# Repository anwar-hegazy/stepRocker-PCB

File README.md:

# stepRocker-PCB
Eagle Design Files for the stepRocker Stepper Driver Board

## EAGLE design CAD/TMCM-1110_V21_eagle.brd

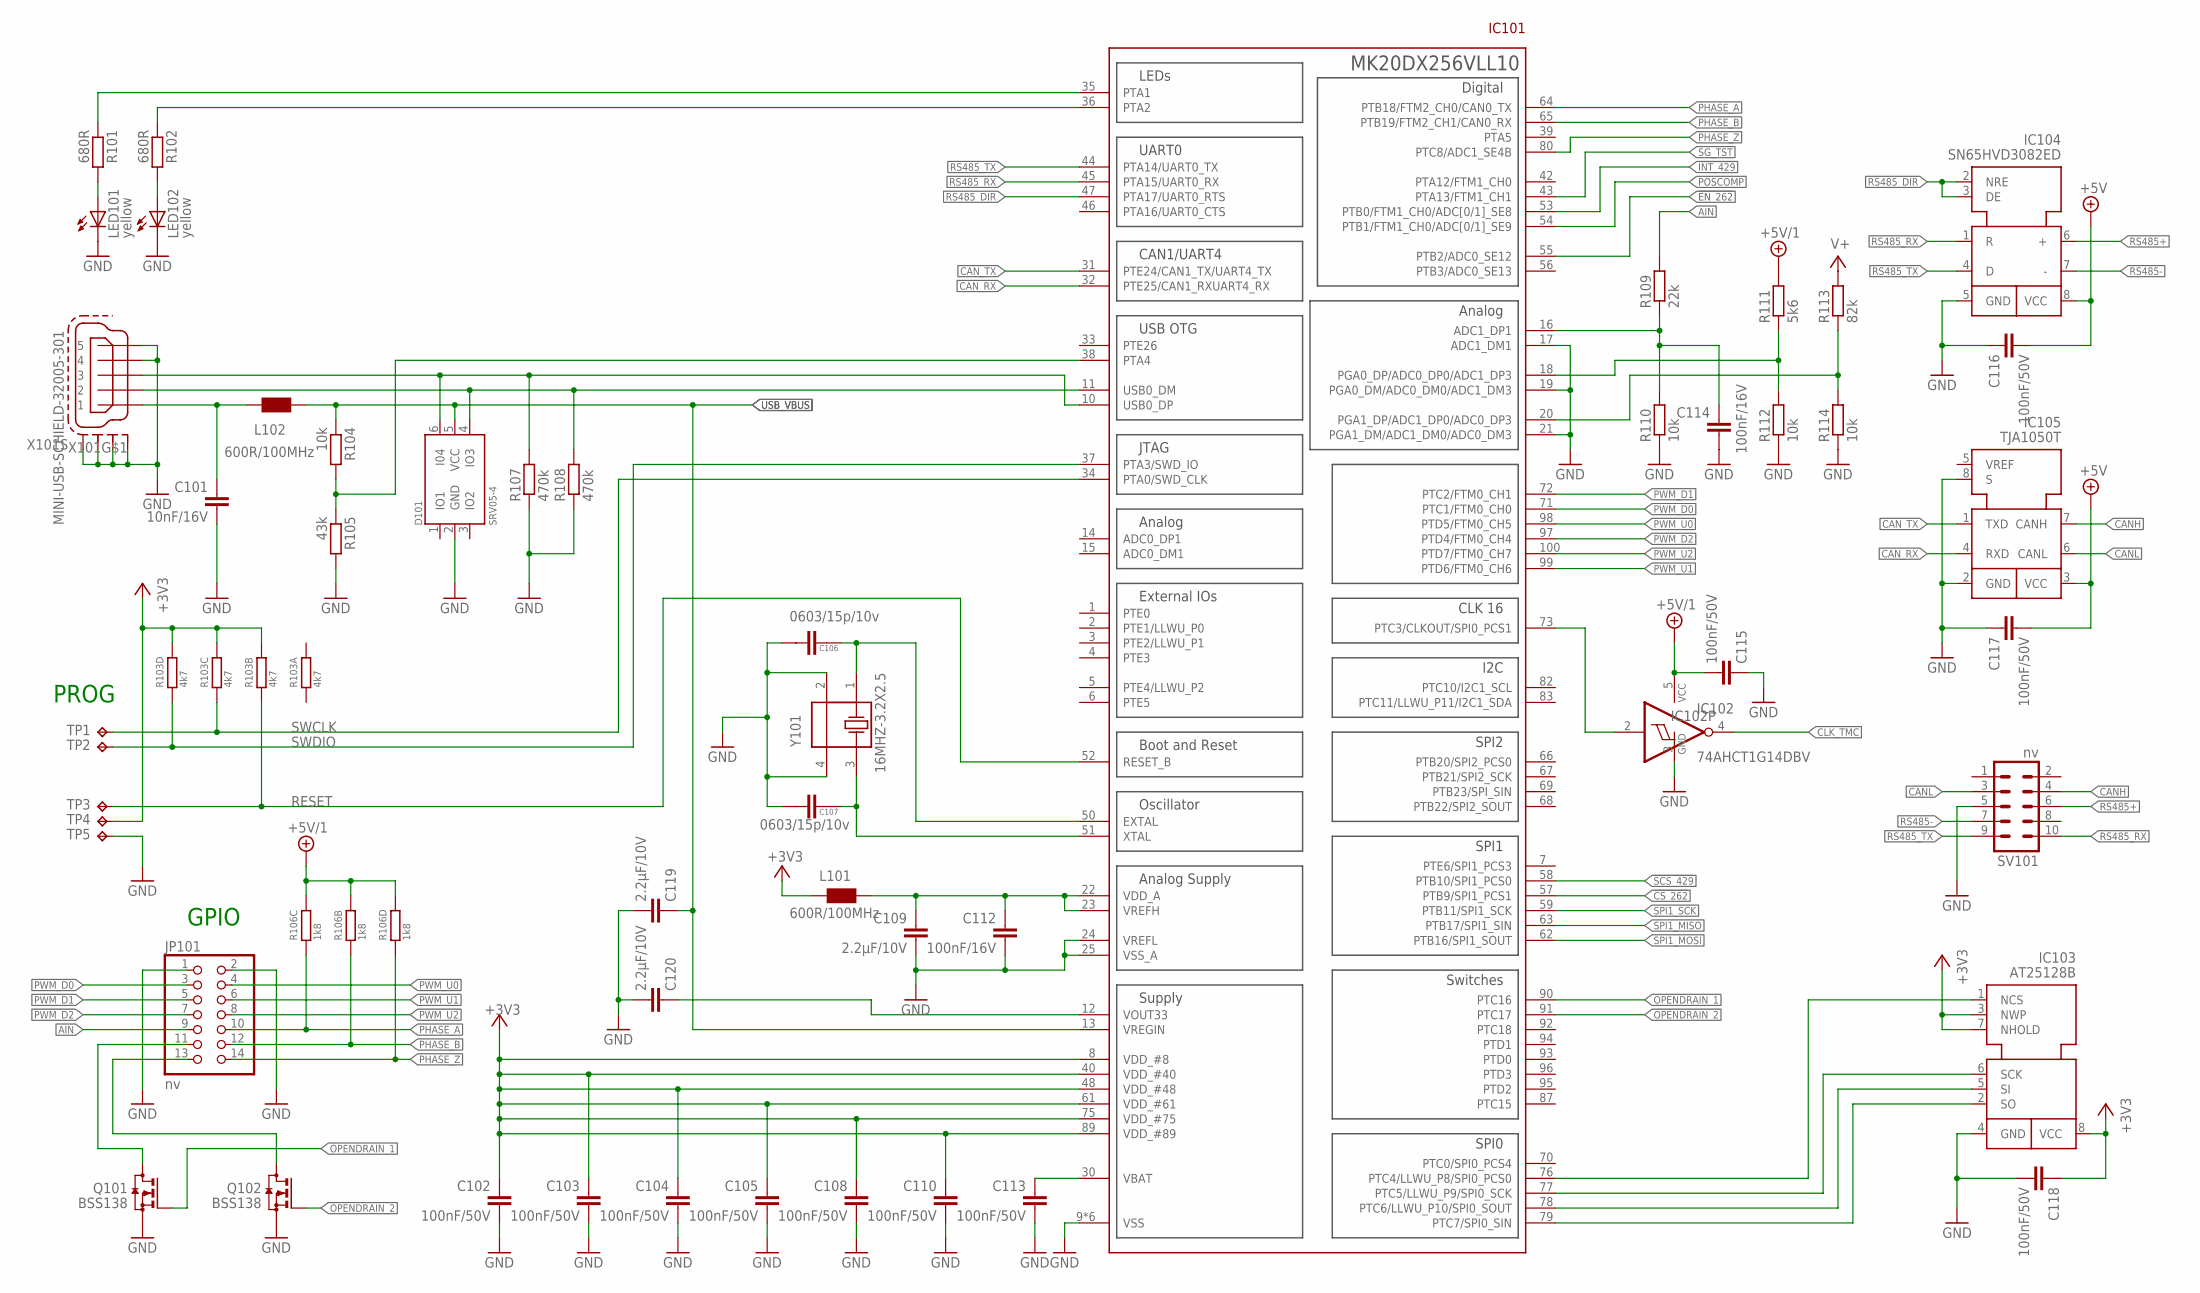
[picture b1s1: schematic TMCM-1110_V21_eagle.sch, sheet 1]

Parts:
C101: 10nF/16V; C0603
C102, C103, C104, C105, C108, C110, C113, C115, C116, C117, C118: 100nF/50V; C0603
C106, C107: 0603/15p/10v; 0603
C109, C119, C120: 2.2µF/10V; C0603
C112, C114: 100nF/16V; C0603
D101: SRV05-4; TMC_SOT23-6
IC101: MK20DX256VLL10; TMC_LQFP100
IC102: 74AHCT1G14DBV; SOT23-5
IC103: AT25128B; SO8
IC104: SN65HVD3082ED; SO8
IC105: TJA1050T; SO8
JP101: nv; 2X07
L101, L102: 600R/100MHz; 0603
LED101, LED102: yellow; CHIP-LED0603
Q101, Q102: BSS138; SOT23
R101, R102: 680R; R0603
R103: 4k7; R_4X_1206
R104, R110, R112, R114: 10k; R0603
R105: 43k; R0603
R106: 1k8; R_4X_1206
R107, R108: 470k; R0603
R109: 22k; R0603
R111: 5k6; R0603
R113: 82k; R0603
SV101: nv; ML10
TP1, TP2, TP3, TP4, TP5: TPTP15SQ; TP15SQ
X101: MINI-USB-SCHIELD-32005-301; 32005-301
Y101: 16MHZ-3.2X2.5; MYLIB_FA-238

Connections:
!CS_262: IC101.57 (PTB9/SPI1_PCS1); also elsewhere on the board
!CS_EEPROM: IC101.76 (PTC4/LLWU_P8/SPI0_PCS0), IC103.1 (NCS)
!EN_262: IC101.55 (PTB2/ADC0_SE12); also elsewhere on the board
!INT_429: IC101.53 (PTB0/FTM1_CH0/ADC[0/1]_SE8); also elsewhere on the board
!SCS_429: IC101.58 (PTB10/SPI1_PCS0); also elsewhere on the board
+3V3: C102.1, C103.1, C104.1, C105.1, C108.1, C110.1, C118.1, IC101.8 (VDD_#8), IC101.40 (VDD_#40), IC101.48 (VDD_#48), IC101.61 (VDD_#61), IC101.75 (VDD_#75), IC101.89 (VDD_#89), IC103.3 (NWP), IC103.7 (NHOLD), IC103.8 (VCC), L101.1, R103.P$5 (2), R103.P$6 (2), R103.P$7 (2), TP4.TP; also elsewhere on the board
+5V: C116.2, C117.2, IC104.8 (VCC), IC105.3 (VCC); also elsewhere on the board
+5V/1: C115.2, IC102.5 (VCC), R106.P$5 (2), R106.P$6 (2), R106.P$7 (2), R111.2; also elsewhere on the board
AIN: JP101.9, R109.2
CANH: IC105.7 (CANH), SV101.4
CANL: IC105.6 (CANL), SV101.3
CAN_RX: IC101.32 (PTE25/CAN1_RXUART4_RX), IC105.4 (RXD)
CAN_TX: IC101.31 (PTE24/CAN1_TX/UART4_TX), IC105.1 (TXD)
CLK_TMC: IC102.4 (O); also elsewhere on the board
GND: C101.2, C102.2, C103.2, C104.2, C105.2, C106.1, C107.1, C108.2, C109.2, C110.2, C112.2, C113.2, C114.2, C115.1, C116.1, C117.1, C118.2, C119.2, C120.2, D101.2 (GND), IC101.9 (VSS), IC101.17 (ADC1_DM1), IC101.19 (PGA0_DM/ADC0_DM0/ADC1_DM3), IC101.21 (PGA1_DM/ADC1_DM0/ADC0_DM3), IC101.24 (VREFL), IC101.25 (VSS_A), IC101.41 (VSS), IC101.49 (VSS), IC101.60 (VSS), IC101.74 (VSS), IC101.88 (VSS), IC102.3 (GND), IC103.4 (GND), IC104.5 (GND), IC105.2 (GND), IC105.8 (S), JP101.1, JP101.2, LED101.C, LED102.C, Q101.2 (S), Q102.2 (S), R105.2, R107.1, R108.1, R110.1, R112.1, R114.1, SV101.5, TP5.TP, X101.4, X101.5, X101.M1 (S1), X101.M2 (S2), X101.M3 (S3), X101.M4 (S4), Y101.2, Y101.4; also elsewhere on the board
unnamed: IC101.73 (PTC3/CLKOUT/SPI0_PCS1), IC102.2 (I)
unnamed: IC101.38 (PTA4), R104.2, R105.1
unnamed: JP101.11, Q101.3 (D)
unnamed: IC101.35 (PTA1), R101.1
unnamed: D101.6 (I04), IC101.10 (USB0_DP), R107.2, X101.3
unnamed: D101.4 (IO3), IC101.11 (USB0_DM), R108.2, X101.2
unnamed: LED101.A, R101.2
unnamed: LED102.A, R102.2
unnamed: C109.1, C112.1, IC101.22 (VDD_A), IC101.23 (VREFH), L101.2
unnamed: IC101.36 (PTA2), R102.1
unnamed: C114.1, IC101.16 (ADC1_DP1), R109.1, R110.2
unnamed: C113.1, IC101.30 (VBAT)
unnamed: C106.2, IC101.50 (EXTAL), Y101.1
unnamed: C101.1, L102.1, X101.1
unnamed: C107.2, IC101.51 (XTAL), Y101.3
unnamed: IC101.18 (PGA0_DP/ADC0_DP0/ADC1_DP3), R111.1, R112.2
unnamed: IC101.20 (PGA1_DP/ADC1_DP0/ADC0_DP3), R113.1, R114.2
unnamed: JP101.13, Q102.3 (D)
unnamed: C120.1, IC101.12 (VOUT33)
OPENDRAIN_1: IC101.90 (PTC16), Q101.1 (G)
OPENDRAIN_2: IC101.91 (PTC17), Q102.1 (G)
PHASE_A: IC101.64 (PTB18/FTM2_CH0/CAN0_TX), JP101.10, R106.P$3 (1)
PHASE_B: IC101.65 (PTB19/FTM2_CH1/CAN0_RX), JP101.12, R106.P$2 (1)
PHASE_Z: IC101.80 (PTC8/ADC1_SE4B), JP101.14, R106.P$4 (1)
POSCOMP: IC101.54 (PTB1/FTM1_CH0/ADC[0/1]_SE9); also elsewhere on the board
PWM_D0: IC101.71 (PTC1/FTM0_CH0), JP101.3
PWM_D1: IC101.72 (PTC2/FTM0_CH1), JP101.5
PWM_D2: IC101.97 (PTD4/FTM0_CH4), JP101.7
PWM_U0: IC101.98 (PTD5/FTM0_CH5), JP101.4
PWM_U1: IC101.99 (PTD6/FTM0_CH6), JP101.6
PWM_U2: IC101.100 (PTD7/FTM0_CH7), JP101.8
RESET: IC101.52 (RESET_B), R103.P$2 (1), TP3.TP
RS485+: IC104.6 (+), SV101.6
RS485-: IC104.7 (-), SV101.7
RS485_DIR: IC101.47 (PTA17/UART0_RTS), IC104.2 (NRE), IC104.3 (DE)
RS485_RX: IC101.45 (PTA15/UART0_RX), IC104.1 (R), SV101.10
RS485_TX: IC101.44 (PTA14/UART0_TX), IC104.4 (D), SV101.9
SG_TST: IC101.43 (PTA13/FTM1_CH1); also elsewhere on the board
SPI0_MISO: IC101.79 (PTC7/SPI0_SIN), IC103.2 (SO)
SPI0_MOSI: IC101.78 (PTC6/LLWU_P10/SPI0_SOUT), IC103.5 (SI)
SPI0_SCK: IC101.77 (PTC5/LLWU_P9/SPI0_SCK), IC103.6 (SCK)
SPI1_MISO: IC101.63 (PTB17/SPI1_SIN); also elsewhere on the board
SPI1_MOSI: IC101.62 (PTB16/SPI1_SOUT); also elsewhere on the board
SPI1_SCK: IC101.59 (PTB11/SPI1_SCK); also elsewhere on the board
SWCLK: IC101.34 (PTA0/SWD_CLK), R103.P$3 (1), TP1.TP
SWDIO: IC101.37 (PTA3/SWD_IO), R103.P$4 (1), TP2.TP
USB_VBUS: C119.1, D101.5 (VCC), IC101.13 (VREGIN), L102.2, R104.1; also elsewhere on the board
V+: R113.2; also elsewhere on the board

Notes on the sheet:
GPIO
PROG

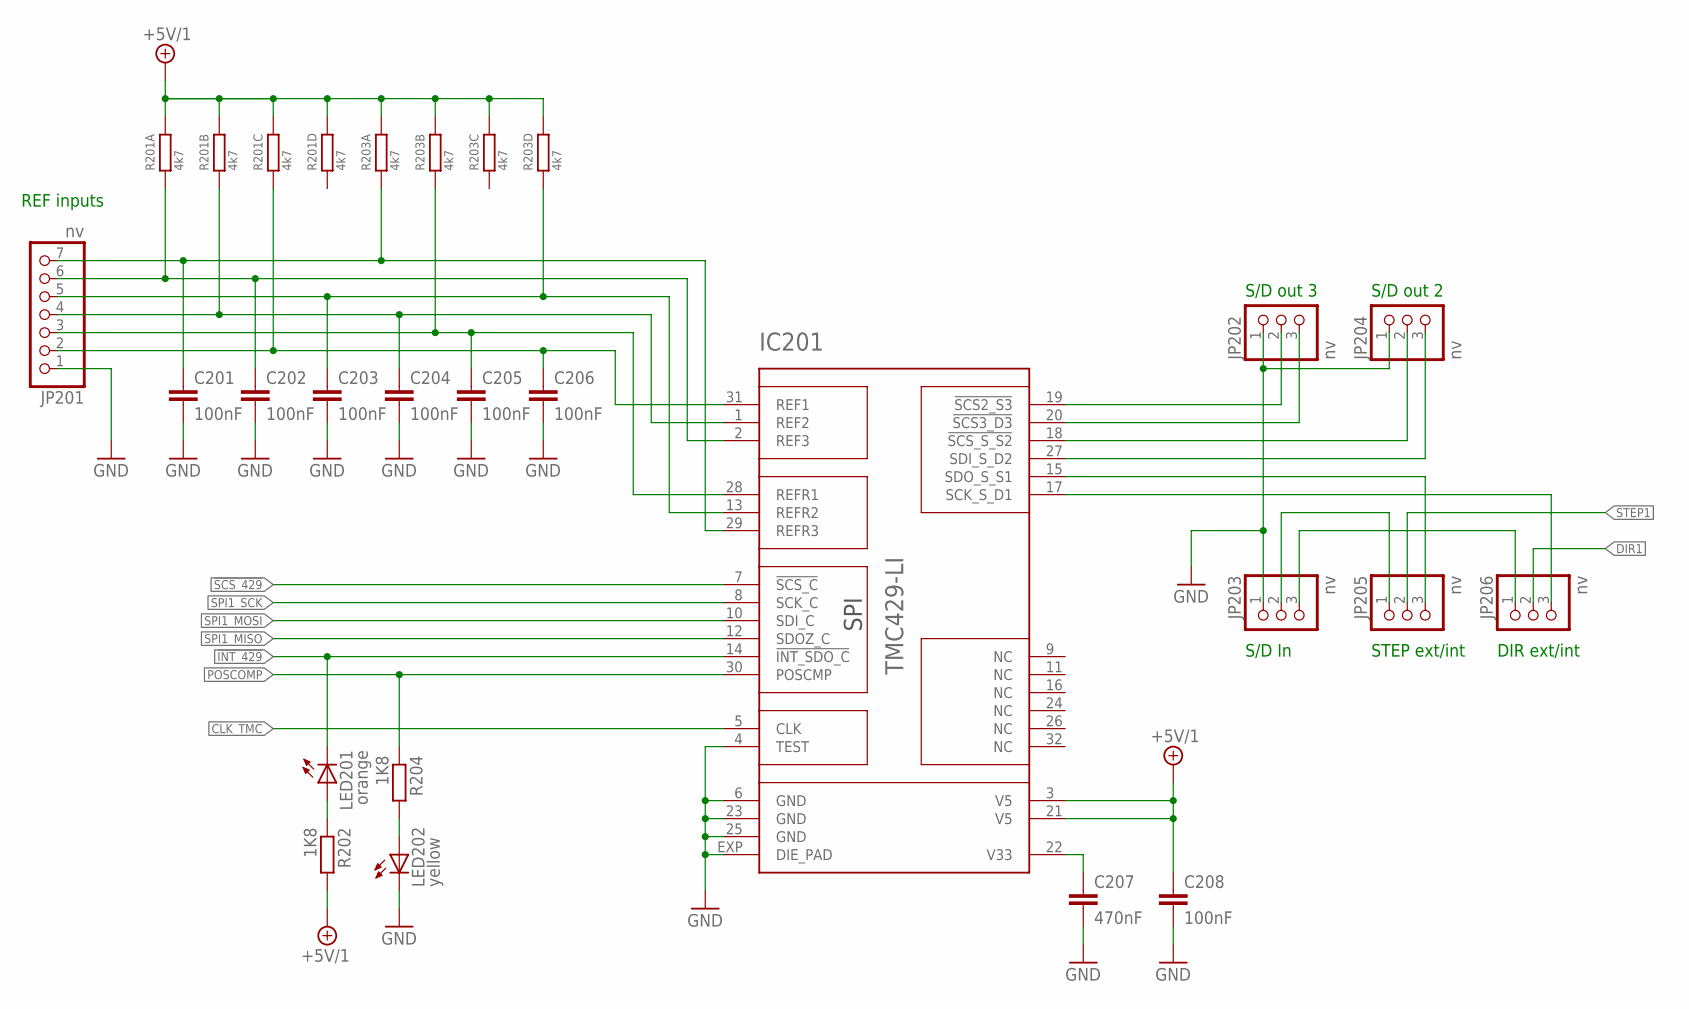
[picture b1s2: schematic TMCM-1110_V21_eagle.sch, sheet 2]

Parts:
C201, C202, C203, C204, C205, C206, C208: 100nF; C0603
C207: 470nF; C0603
IC201: TMC429-LI; QFN32_5X5
JP201: nv; 1X07
JP202, JP203, JP204, JP205, JP206: nv; 1X03
LED201: orange; CHIP-LED0603
LED202: yellow; CHIP-LED0603
R201, R203: 4k7; R_4X_1206
R202, R204: 1K8; R0603

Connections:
!INT_429: IC201.14 (!INT_SDO_C), LED201.C; also elsewhere on the board
!SCS_429: IC201.7 (!SCS_C); also elsewhere on the board
+5V/1: C208.1, IC201.3 (V5), IC201.21 (V5), R201.P$5 (2), R201.P$6 (2), R201.P$7 (2), R201.P$8 (2), R202.2, R203.P$5 (2), R203.P$6 (2), R203.P$7 (2), R203.P$8 (2); also elsewhere on the board
CLK_TMC: IC201.5 (CLK); also elsewhere on the board
DIR1: JP206.2; also elsewhere on the board
DIR1_429: IC201.17 (SCK_S_D1), JP206.3
DIR1_EXT: JP203.3, JP206.1
DIR2: IC201.27 (SDI_S_D2), JP204.3
DIR3: IC201.20 (!SCS3_D3), JP202.3
GND: C201.2, C202.2, C203.2, C204.2, C205.2, C206.2, C207.2, C208.2, IC201.4 (TEST), IC201.6 (GND), IC201.23 (GND), IC201.25 (GND), IC201.EXP (DIE_PAD), JP201.1, JP202.1, JP203.1, JP204.1, LED202.C; also elsewhere on the board
unnamed: LED202.A, R204.2
unnamed: LED201.A, R202.1
POSCOMP: IC201.30 (POSCMP), R204.1; also elsewhere on the board
REF1: C206.1, IC201.31 (REF1), JP201.2, R201.P$3 (1)
REF2: C204.1, IC201.1 (REF2), JP201.4, R201.P$2 (1)
REF3: C202.1, IC201.2 (REF3), JP201.6, R201.P$1 (1)
REFR1: C205.1, IC201.28 (REFR1), JP201.3, R203.P$2 (1)
REFR2: C203.1, IC201.13 (REFR2), JP201.5, R203.P$4 (1)
REFR3: C201.1, IC201.29 (REFR3), JP201.7, R203.P$1 (1)
SPI1_MISO: IC201.12 (SDOZ_C); also elsewhere on the board
SPI1_MOSI: IC201.10 (SDI_C); also elsewhere on the board
SPI1_SCK: IC201.8 (SCK_C); also elsewhere on the board
STEP1: JP205.2; also elsewhere on the board
STEP1_429: IC201.15 (SDO_S_S1), JP205.3
STEP1_EXT: JP203.2, JP205.1
STEP2: IC201.18 (!SCS_S_S2), JP204.2
STEP3: IC201.19 (!SCS2_S3), JP202.2
V33: C207.1, IC201.22 (V33)

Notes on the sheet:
REF inputs
S/D out 3
S/D out 2
S/D In
STEP ext/int
DIR ext/int

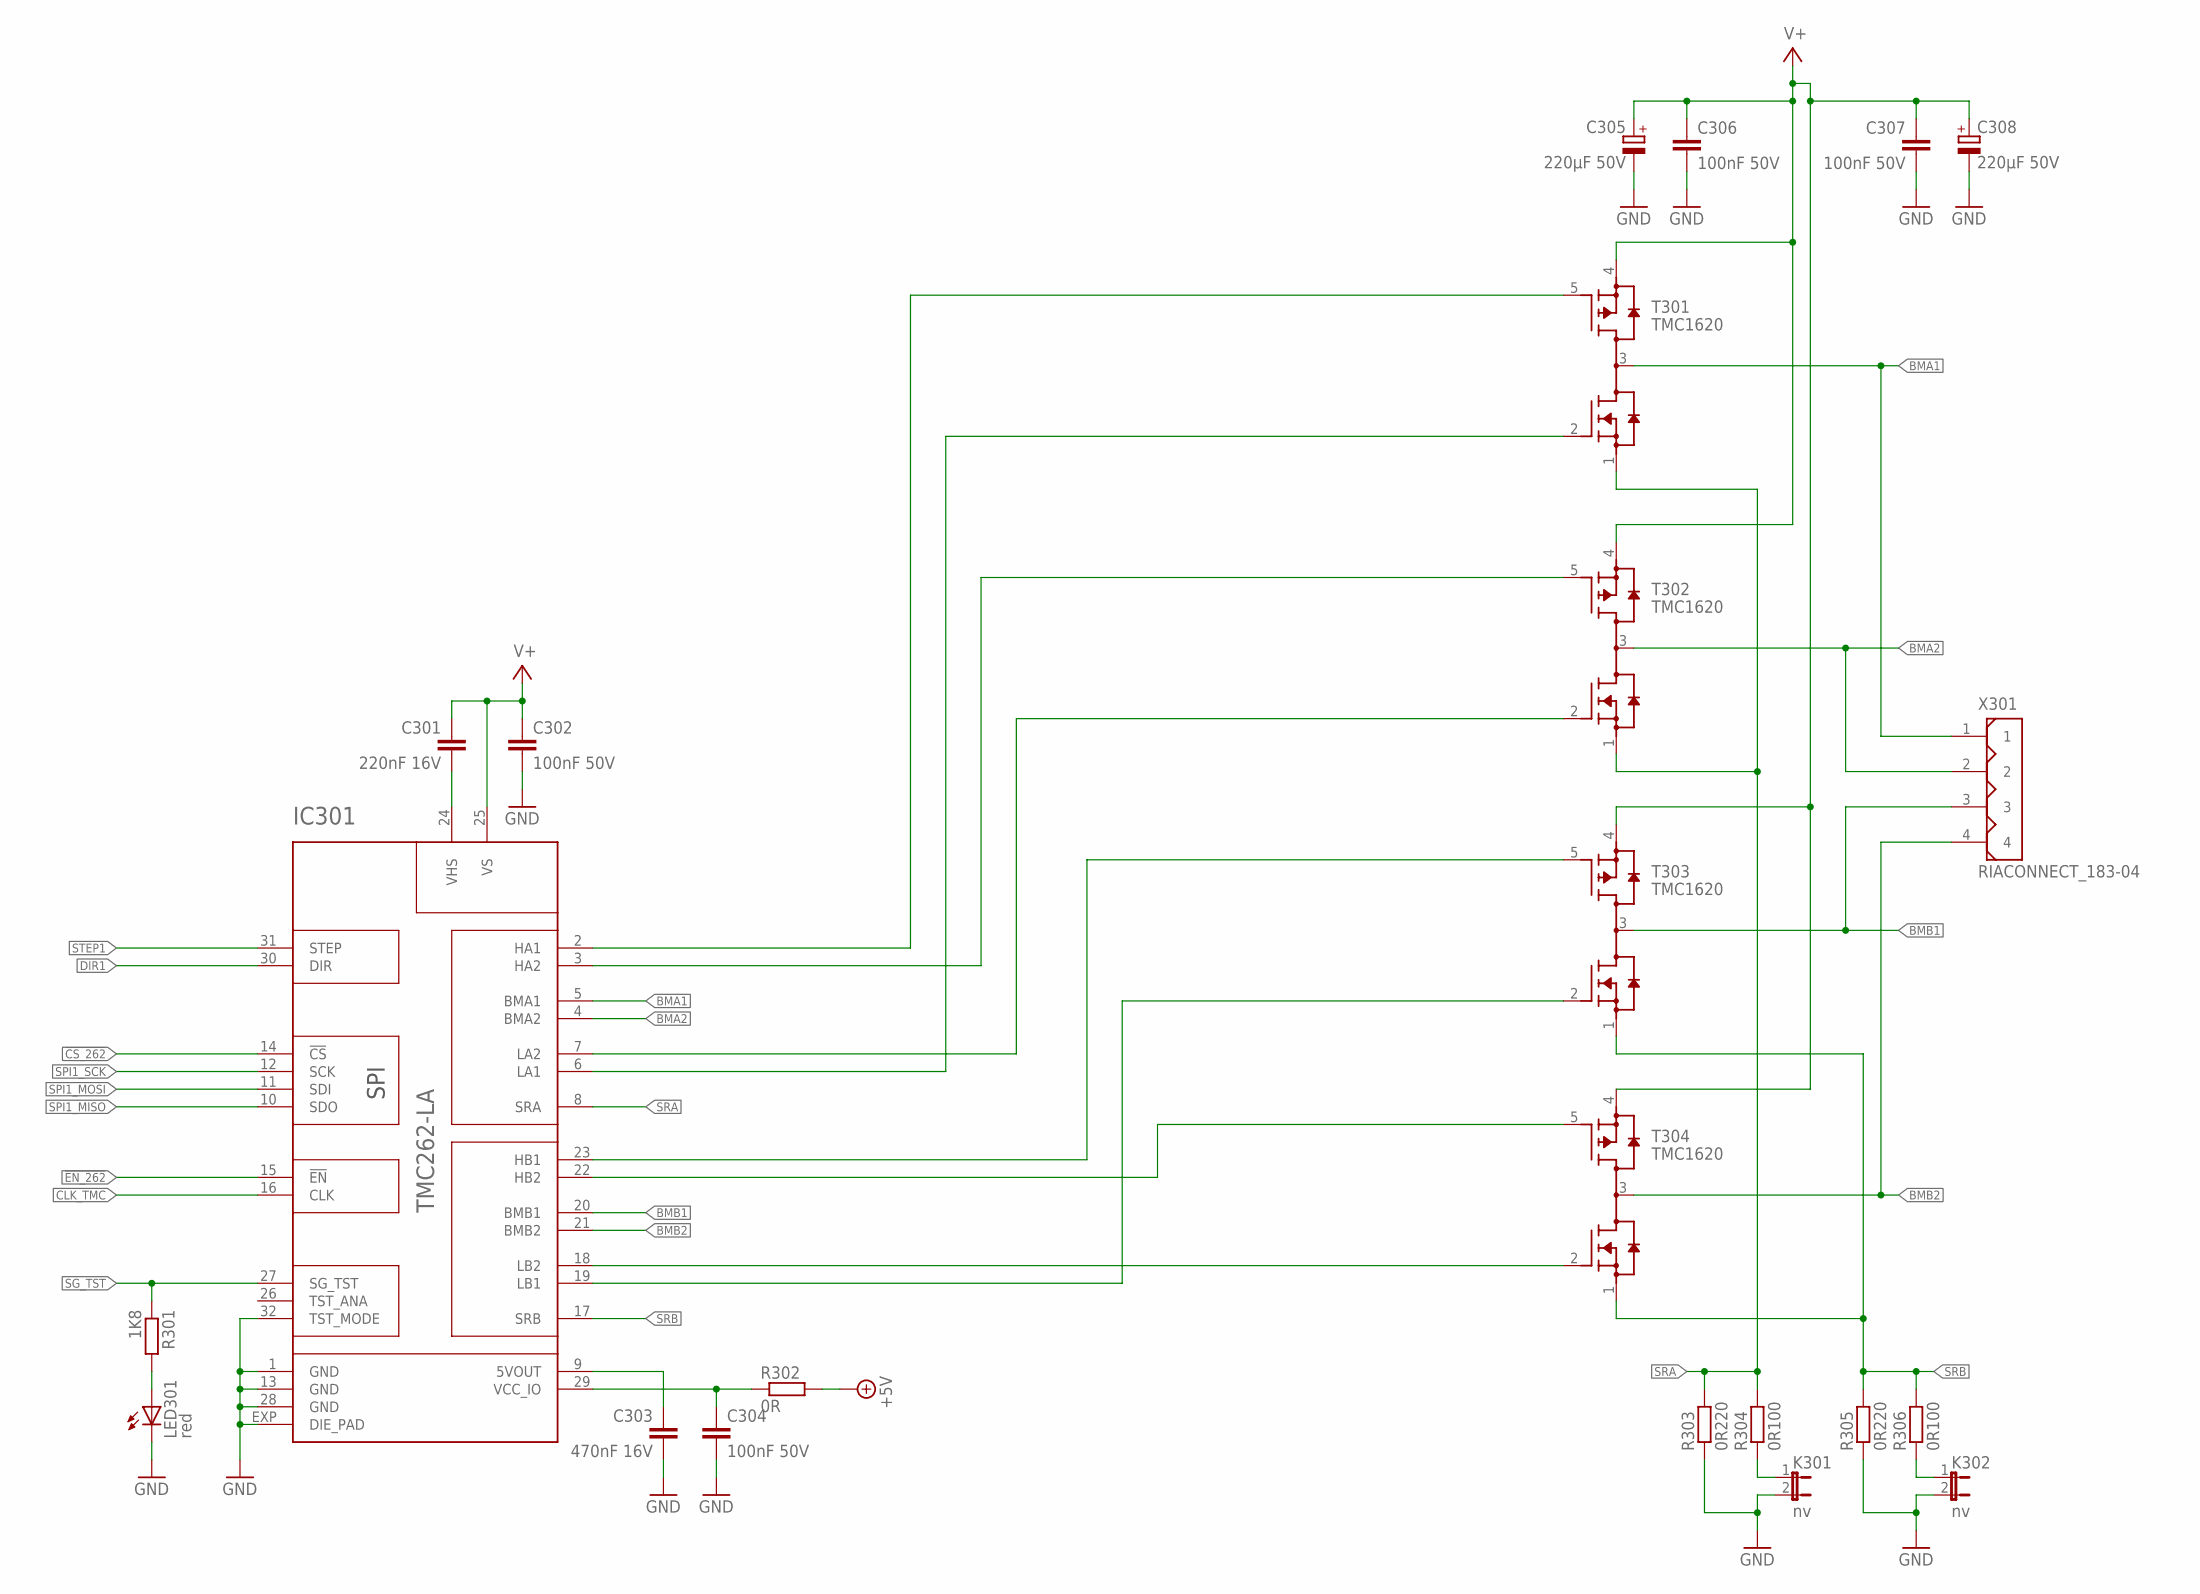
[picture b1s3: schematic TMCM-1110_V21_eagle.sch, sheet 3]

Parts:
C301: 220nF 16V; C0603
C302, C304, C306, C307: 100nF 50V; C0603
C303: 470nF 16V; C0603
C305, C308: 220µF 50V; E5-10,5
IC301: TMC262-LA; QFN32_5X5
K301, K302: nv; JP1
LED301: red; CHIP-LED0603
R301: 1K8; R0603
R302: 0R; R0603
R303, R305: 0R220; R1206
R304, R306: 0R100; R1206
T301, T302, T303, T304: TMC1620; DUAL_DPAK_4L
X301: RIACONNECT_183-04

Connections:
!CS_262: IC301.14 (!CS); also elsewhere on the board
!EN_262: IC301.15 (!EN); also elsewhere on the board
+5V: R302.2; also elsewhere on the board
BMA1: IC301.5 (BMA1), T301.3 (D_NP), X301.1
BMA2: IC301.4 (BMA2), T302.3 (D_NP), X301.2
BMB1: IC301.20 (BMB1), T303.3 (D_NP), X301.3
BMB2: IC301.21 (BMB2), T304.3 (D_NP), X301.4
CLK_TMC: IC301.16 (CLK); also elsewhere on the board
DIR1: IC301.30 (DIR); also elsewhere on the board
GND: C302.2, C303.2, C304.2, C305.-, C306.2, C307.2, C308.-, IC301.1 (GND), IC301.13 (GND), IC301.28 (GND), IC301.32 (TST_MODE), IC301.EXP (DIE_PAD), K301.2, K302.2, LED301.C, R303.1, R305.1; also elsewhere on the board
unnamed: LED301.A, R301.2
unnamed: C304.1, IC301.29 (VCC_IO), R302.1
unnamed: C303.1, IC301.9 (5VOUT)
unnamed: C301.2, IC301.24 (VHS)
unnamed: IC301.2 (HA1), T301.5 (G_P)
unnamed: IC301.3 (HA2), T302.5 (G_P)
unnamed: IC301.7 (LA2), T302.2 (G_N)
unnamed: IC301.6 (LA1), T301.2 (G_N)
unnamed: IC301.23 (HB1), T303.5 (G_P)
unnamed: IC301.22 (HB2), T304.5 (G_P)
unnamed: IC301.19 (LB1), T303.2 (G_N)
unnamed: IC301.18 (LB2), T304.2 (G_N)
unnamed: K302.1, R306.1
unnamed: K301.1, R304.1
SG_TST: IC301.27 (SG_TST), R301.1; also elsewhere on the board
SPI1_MISO: IC301.10 (SDO); also elsewhere on the board
SPI1_MOSI: IC301.11 (SDI); also elsewhere on the board
SPI1_SCK: IC301.12 (SCK); also elsewhere on the board
SRA: IC301.8 (SRA), R303.2, R304.2, T301.1 (S_N), T302.1 (S_N)
SRB: IC301.17 (SRB), R305.2, R306.2, T303.1 (S_N), T304.1 (S_N)
STEP1: IC301.31 (STEP); also elsewhere on the board
V+: C301.1, C302.1, C305.+, C306.1, C307.1, C308.+, IC301.25 (VS), T301.4 (S_P), T302.4 (S_P), T303.4 (S_P), T304.4 (S_P); also elsewhere on the board

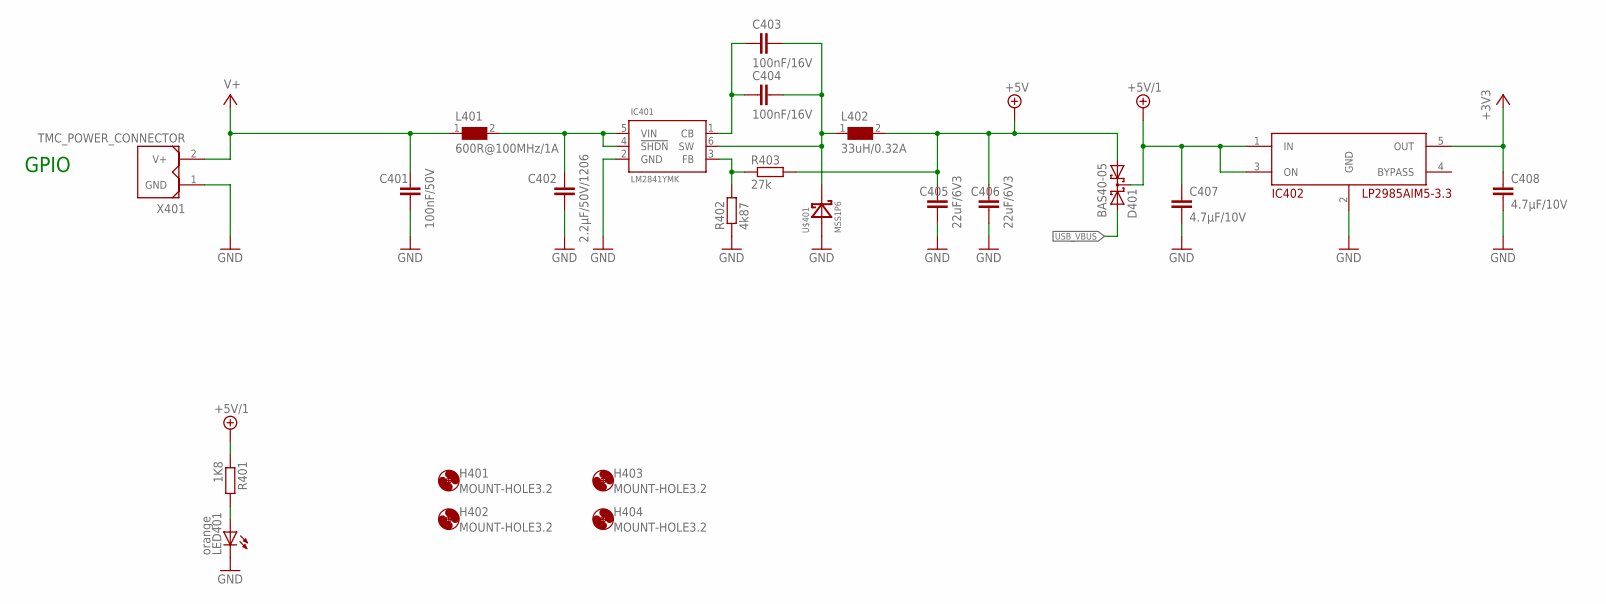
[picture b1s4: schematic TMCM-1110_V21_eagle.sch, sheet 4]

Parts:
C401: 100nF/50V; C0603
C402: 2.2µF/50V/1206; C1206
C403, C404: 100nF/16V; C0603
C405, C406: 22uF/6V3; C0805
C407, C408: 4.7µF/10V; C0603
D401: BAS40-05; SOT23
H401, H402, H403, H404: MOUNT-HOLE3.2; 3,2
IC401: LM2841YMK; TMC_SOT23-6
IC402: LP2985AIM5-3.3; SOT23-5
L401: 600R@100MHz/1A; 0603
L402: 33uH/0.32A; WE-TPC_3816
LED401: orange; CHIP-LED0603
R401: 1K8; R0603
R402: 4k87; R0603
R403: 27k; R0603
U$401: MSS1P6; MICRO_SMP
X401: TMC_POWER_CONNECTOR; RIACONNECT_320-02

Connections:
+3V3: C408.1, IC402.5 (OUT); also elsewhere on the board
+5V: C405.1, C406.1, D401.1 (A1), L402.2, R403.2; also elsewhere on the board
+5V/1: C407.1, D401.3 (C), IC402.1 (IN), IC402.3 (ON), R401.1; also elsewhere on the board
GND: C401.2, C402.2, C405.2, C406.2, C407.2, C408.2, IC401.2 (GND), IC402.2 (GND), LED401.C, R402.1, U$401.A, X401.1 (GND); also elsewhere on the board
unnamed: C403.1, C404.1, IC401.1 (CB)
unnamed: C403.2, C404.2, IC401.6 (SW), L402.1, U$401.C
unnamed: C402.1, IC401.4 (!SHDN), IC401.5 (VIN), L401.2
unnamed: LED401.A, R401.2
unnamed: IC401.3 (FB), R402.2, R403.1
USB_VBUS: D401.2 (A2); also elsewhere on the board
V+: C401.1, L401.1, X401.2 (V+); also elsewhere on the board

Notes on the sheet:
GPIO

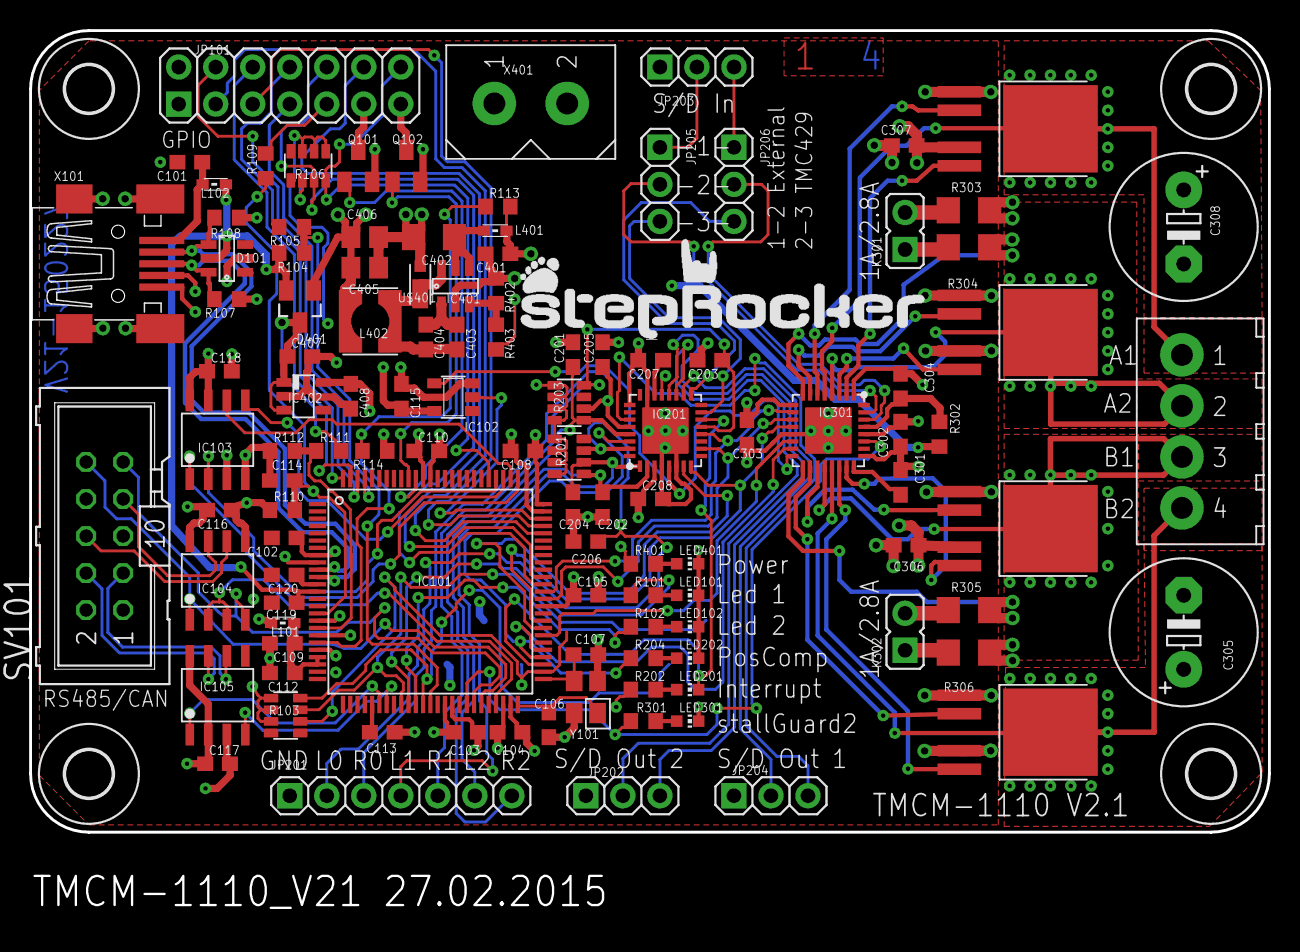
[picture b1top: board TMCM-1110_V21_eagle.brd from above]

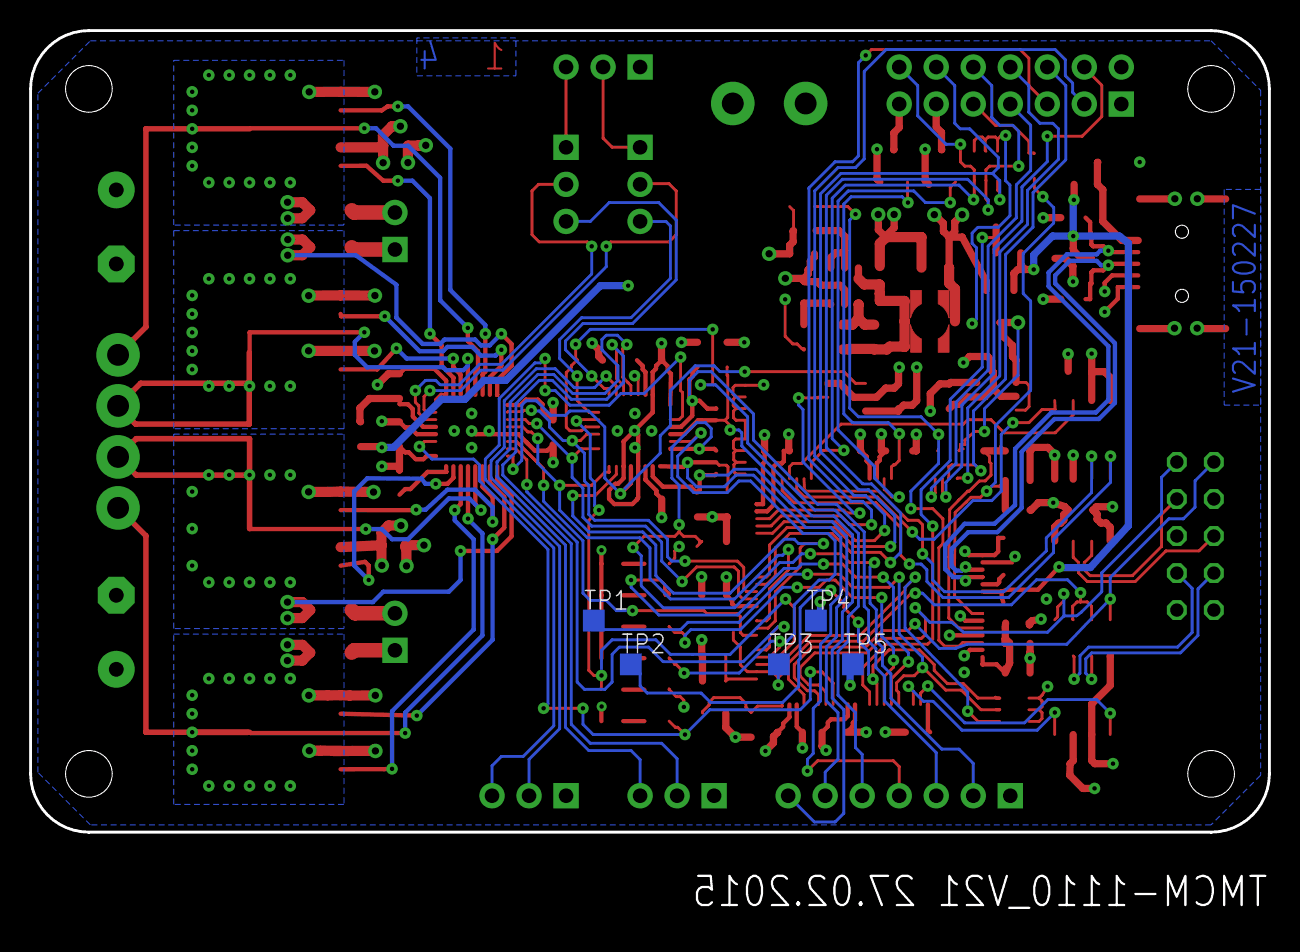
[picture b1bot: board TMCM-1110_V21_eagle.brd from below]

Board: 4 copper layers, 85.0 x 61.1 mm, 122 parts (5 on the bottom side), 107 nets.

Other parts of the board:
DRILEGEND: DRILEGEND

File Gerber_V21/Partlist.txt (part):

Partlist

Exported from TMCM-1110_V21.brd at 27.02.2015 09:53:44

EAGLE Version 6.5.0 Copyright (c) 1988-2013 CadSoft

Assembly variant: 

Part     Value                      Package           Library                    Position (mm)         Orientation

C101     10nF/16V                   C0603             rcl                        (10.922 45.974)       R180
C102     100nF/50V                  C0603             rcl                        (17.399 20.193)       R180
C103     100nF/50V                  C0603             rcl                        (29.845 6.858)        R0
C104     100nF/50V                  C0603             rcl                        (32.893 6.858)        R0
C105     100nF/50V                  C0603             rcl                        (38.1 16.256)         R0
C106     0603/15p/10v               0603              _TMC_TE_RCL                (35.56 7.366)         R90
C107     0603/15p/10v               0603              _TMC_TE_RCL                (38.1 12.192)         R180
C108     100nF/50V                  C0603             rcl                        (33.782 26.162)       R180
C109     2.2µF/10V                  C0603             rcl                        (17.272 12.954)       R180
C110     100nF/50V                  C0603             rcl                        (27.178 26.162)       R0
C112     100nF/16V                  C0603             rcl                        (17.272 10.922)       R180
C113     100nF/50V                  C0603             rcl                        (24.13 6.858)         R0
C114     100nF/16V                  C0603             rcl                        (17.272 24.13)        R180
C115     100nF/50V                  C0603             rcl                        (25.4475 29.9085)     R270
C116     100nF/50V                  C0603             rcl                        (12.954 22.098)       R180
C117     100nF/50V                  C0603             rcl                        (12.827 4.699)        R0
C118     100nF/50V                  C0603             rcl                        (12.954 31.623)       R0
C119     2.2µF/10V                  C0603             rcl                        (17.399 15.748)       R180
C120     2.2µF/10V                  C0603             rcl                        (17.399 17.653)       R180
C201     100nF                      C0603             rcl                        (37.211 32.766)       R90
C202     100nF                      C0603             rcl                        (39.243 22.479)       R270
C203     100nF                      C0603             rcl                        (46.609 32.385)       R180
C204     100nF                      C0603             rcl                        (37.211 22.479)       R270
C205     100nF                      C0603             rcl                        (39.243 32.766)       R90
C206     100nF                      C0603             rcl                        (38.1 19.939)         R180
C207     470nF                      C0603             rcl                        (42.545 32.385)       R180
C208     100nF                      C0603             rcl                        (42.545 22.86)        R0
C301     220nF 16V                  C0603             rcl                        (59.69 24.003)        R270
C302     100nF 50V                  C0603             rcl                        (59.69 27.305)        R90
C303     470nF 16V                  C0603             rcl                        (49.149 27.432)       R270
C304     100nF 50V                  C0603             rcl                        (59.69 30.607)        R90
C305     220µF 50V                  E5-10,5           rcl                        (79.121 13.716)       R90
C306     100nF 50V                  C0603             rcl                        (60.071 19.685)       R180
C307     100nF 50V                  C0603             rcl                        (59.944 47.117)       R180
C308     220µF 50V                  E5-10,5           rcl                        (79.121 41.529)       R270
C401     100nF/50V                  C0603             rcl                        (32.0675 39.6875)     R180
C402     2.2µF/50V/1206             C1206             rcl                        (27.686 40.8305)      R180
C403     100nF/16V                  C0603             rcl                        (29.2735 33.9725)     R270
C404     100nF/16V                  C0603             rcl                        (27.1145 33.9725)     R270
C405     22uF/6V3                   C0805             rcl                        (22.9235 38.735)      R0
C406     22uF/6V3                   C0805             rcl                        (22.9235 40.8305)     R0
C407     4.7µF/10V                  C0603             rcl                        (18.4785 32.639)      R0
C408     4.7µF/10V                  C0603             rcl                        (21.971 29.9085)      R270
D101     SRV05-4                    TMC_SOT23-6       TMC_IC                     (13.462 39.37)        R90
D401     BAS40-05                   SOT23             diode                      (18.4785 36.068)      R180
IC101    MK20DX256VLL10             TMC_LQFP100       TMC_IC                     (27.432 16.51)        R270
IC102    74AHCT1G14DBV              SOT23-5           74xx-little-us             (29.0035 29.845)      R90
IC103    AT25128B                   SO8               stepRocker                 (12.827 26.924)       R90
IC104    SN65HVD3082ED              SO8               stepRocker                 (12.827 17.272)       R90
IC105    TJA1050T                   SO8               stepRocker                 (12.827 9.398)        R90
IC201    TMC429-LI                  QFN32_5X5         stepRocker                 (43.561 27.559)       R90
IC301    TMC262-LA                  QFN32_5X5         stepRocker                 (54.737 27.559)       R270
IC401    LM2841YMK                  TMC_SOT23-6       TMC_IC                     (29.1465 37.465)      R0
IC402    LP2985AIM5-3.3             SOT23-5           stepRocker                 (18.7325 29.9085)     R270
JP101    nv                         2X07              pinhead                    (17.78 51.23)         R0
JP201    nv                         1X07              pinhead                    (25.4 2.5)            R0
JP202    nv                         1X03              pinhead                    (40.64 2.5)           R0
JP203    nv                         1X03              pinhead                    (45.72 52.5)          R0
JP204    nv                         1X03              pinhead                    (50.8 2.5)            R0
JP205    nv                         1X03              pinhead                    (43.18 44.45)         R270
JP206    nv                         1X03              pinhead                    (48.26 44.45)         R270
K301     nv                         JP1               jumper                     (60 41.25)            R0
K302     nv                         JP1               jumper                     (60 13.75)            R0
L101     600R/100MHz                0603              wuerth-elektronik          (17.399 14.351)       R0
L102     600R/100MHz                0603              wuerth-elektronik          (12.7 44.45)          R0
L401     600R@100MHz/1A             0603              Wuerth_Elektronik_eiSos_V6 (31.877 41.275)       R180
L402     33uH/0.32A                 WE-TPC_3816       Wuerth_Elektronik_eiSos_V6 (23.3045 35.052)      R180
LED101   yellow                     CHIP-LED0603      led                        (45.085 16.256)       R270
LED102   yellow                     CHIP-LED0603      led                        (45.085 14.097)       R270
LED201   orange                     CHIP-LED0603      led                        (45.085 9.779)        R270
LED202   yellow                     CHIP-LED0603      led                        (45.085 11.938)       R270
LED301   red                        CHIP-LED0603      led                        (45.085 7.62)         R270
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
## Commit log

2015-08-26 stepRocker Gerber Data V1.1 added
2015-08-26 Added newer versions and related information

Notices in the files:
parts and their libraries:
Wuerth_Elektronik_eiSos_V6: Copyright: Würth Elektronik
